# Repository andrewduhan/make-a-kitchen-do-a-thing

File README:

== Make A Kitchen Do A Thing ==

Preview: http://dl.dropbox.com/u/126001/circuits/kitchen-layout_and_board.jpg

=== Description ===
This is an Arduino clone with handy connections for 8 physical inputs and 8 high(er) current outputs, a built-in ULN2803 darlington array (http://www.ti.com/lit/ds/symlink/uln2803a.pdf), and selectable output voltage.  The project began as a way to add lights and stuff to my daughter's play kitchen, but turned into a more general-purpose board.

Inputs and outputs have 2.0mm JST right-angle locking connectors (http://media.digikey.com/pdf/Data%20Sheets/JST%20PDFs/PH%20Series.pdf).  There are also pads to wire in whatever you'd like.

=== Inputs ===
Four inputs are wired for switches (digital) and four have three pins to connect to a pot/knob (analog).  Of course you can use them all for something else entirely.   Each input has an LED that indicates the current state of that switch or knob.

=== Outputs ===
Devices connected to an output will see a voltage (either 5V or VIN) when the corresponding processor pin is set LOW. Each output can sink up to 500mA though the transistor, and I wouldn't sink more than 1500mA in total across all eight channels at any one time.  Six of the outputs are on PWM-capable channels.  Each output has an LED that indicates it's current state.

=== Power ===
9-24V DC into the barrel jack or directly onto the pads next to the barrel jack.  The Power LED will light when power is connected.
Output voltage can be set in the center-right of the board.
Set to 5V by wiring the VOUT pad to the 5V pad - this will cause all output power to come through the 7805 voltage regulator, and therefore limits your total current consumption to 1A.
Wiring the VOUT pad to the VIN pad will set your outputs to VIN, bypassing the regulator and allowing you to drive higher voltage devices like relays and motors.  The board's internal circuitry will still use 5V, only the output is changed.

=== Software ===
The arduino sketch "basic-kitchen.ino" causes the outputs to reflect the inputs.  This could be a good starting point for your projects.
The six FT232 pins in the center of the board will connect with a standard FTDI-style serial breakout board for programming via USB or such.

----

=== Build Notes ===
* Add the small parts first.
* If you don't like the LEDs, you don't need to install them.   They're just to make programming easier.
* I like to use a chip socket for the processor, but I suggest you solder the ULN2803 directly to the board so that it can thermally couple with the exposed copper beneath.  If you're going to sink a lot of current, maybe dab a bit of heatsink compound under there?

==== rev 19 ====
* The resistor network values aren't marked on the board, whoops.  4 of them are 1k, and the one right next to the processor is 10k.
* The voltage regulator section has markings for both 1000uf (solid line) and 100uf (dashed line) caps. If you're not going to pull a lot of current through the voltage regulator, you can use 100uf.  In BOTH cases, the NEGATIVE pin should go into the ROUND hole.  Whichever you choose, ignore the left over square pad.
* I goofed the silkscreen orientation markings for the LEDS, whoops.  The NEGATIVE/ANODE side with the SHORT pin should go into the ROUND pad.  The POSITIVE/CATHODE side with the LONG pin should go into the SQUARE hole.
* The holes for header pins (like the FT232 block) are really really tight with standard pins.  They'll fit, but you gotta work them gently/firmly back and forth.  Sorry about that.

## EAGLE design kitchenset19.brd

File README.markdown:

#Make A Kitchen Do A Thing

##Description

This is an Arduino clone with handy connections for eight physical inputs and eight high(er) current outputs, a built-in [ULN2803](http://www.ti.com/lit/ds/symlink/uln2803a.pdf) darlington array, per-pin LEDs for easy programming, and selectable output voltage.  The project began as a way to add lights and stuff to my daughter's play kitchen, but turned into a more general-purpose board.

Inputs and outputs have 2.0mm [JST right-angle locking connectors](http://media.digikey.com/pdf/Data%20Sheets/JST%20PDFs/PH%20Series.pdf).  There are also pads to wire in whatever you'd like.

The files were created in the free edition of CadSoft Eagle.

The board makes heavy use of curved traces simply because I think they look neat.  Unfortunately, curved traces are a pain in the ass to work with or edit;   I will add a straight-traces version soon.

###Inputs
Four inputs are wired with two pins for switches for [digital input](http://arduino.cc/en/Reference/digitalRead).  They are "ON" when the signal pin is pulled LOW (connected to the ground pin.) Four inputs have three pins for [analog input](http://arduino.cc/en/Reference/analogRead), like a knob.  This makes it easy to attach a pot to the ground and 5V pins, with the center (wiper) pin moving between 0 and 5V.  Of course you can use them all for something else entirely.  Each input has an LED that indicates the current state of that switch or knob.

###Outputs
Devices connected to an output will see a voltage ( either 5V or VIN, **minus the drop across the transistor**: 1V to 1.5V depending on current) when the corresponding processor pin is set HIGH.  Each output can sink up to 500mA though the transistor, and I wouldn't sink more than 1500mA in total across all eight channels at any one time.  Six of the outputs are on [PWM pins](http://arduino.cc/en/Reference/analogWrite), the other two can only output [On/Off](http://arduino.cc/en/Reference/digitalWrite).  Each output has an LED that indicates it's current state.

###Power
Supply 9-24V DC into the barrel jack or directly onto the pads next to the barrel jack.  The Power LED will light when power is connected.
Output voltage can be selected with the three larger pads marked VIN, VOUT, and 5V in the center-right of the board.
Wiring the VOUT pad to the 5V pad will cause all output power to come through the 7805 voltage regulator, and therefore limits your total current consumption to 1A.
Wiring the VOUT pad to the VIN pad will set your outputs to VIN, bypassing the regulator and allowing you to drive higher voltage devices like relays and motors.  The board's internal circuitry will still use 5V, only the output is changed.

###Software
The arduino sketch "basic-kitchen.ino" has constants defined for the I/O pins and simply makes the outputs to reflect the inputs.  This could be a good starting point for your projects.
The six FT232 pins in the center of the board will connect with a standard FTDI-style serial breakout board for programming via USB, [like this one](http://www.sparkfun.com/products/9716).

###Extras
The Arduino firmware gives the ATMega328 a total of twenty I/O pins.  On this board, sixteen of those are used for the main I/O and two are used for the serial FT232 block.  The remaining two unused pins (digital 2 and 4) are broken out to pads on the left side of the board.

----

###Build Notes
* Add the small parts first.
* If you don't like the LEDs, you don't need to install them.   They're just to make programming easier.
* I like to use a chip socket for the processor, but I suggest you solder the ULN2803 directly to the board so that it can thermally couple with the exposed copper beneath.  If you're going to sink a lot of current, maybe dab a bit of heatsink compound under there?
* Large capacitors:  the NEGATIVE pin goes in the ROUND hole.  The positive can go in either square hole, depending on the size of the cap.

###rev 19 issues
* Output connectors are wired with positive to the LEFT when you look at the board with outputs at the top.  This is actually backwards from what JST connectors usually do, so on pre-made connectors you will have BLACK = POSITIVE.  Whoops.
* The resistor network values aren't marked on the board, whoops.  They are all 1k.
* The voltage regulator section has markings for both 1000uf (solid line) and 100uf (dashed line) caps. If you're not going to pull a lot of current through the voltage regulator, you can use 100uf.  In BOTH cases, the NEGATIVE pin should go into the ROUND hole.  Whichever you choose, ignore the left over square pad.
* I goofed the silkscreen orientation markings for the LEDS, whoops.  The NEGATIVE/ANODE side with the SHORT pin should go into the ROUND pad.  The POSITIVE/CATHODE side with the LONG pin should go into the SQUARE hole.
Specifically: look at the board so you can read "Make a kitchen do a thing" and the outputs are at the top, inputs at the bottom.   All of the output LEDs should have their FLAT side to your LEFT.  The four input LEDs on the left (marked 12-15) should have their FLAT side to your RIGHT.  The other four input LEDS (marked A2-A5) should have their FLAT side to your LEFT.    
* The holes for header pins (like the FT232 block) are really really tight with standard pins.  They'll fit, but you gotta work them gently/firmly back and forth.  Sorry about that.

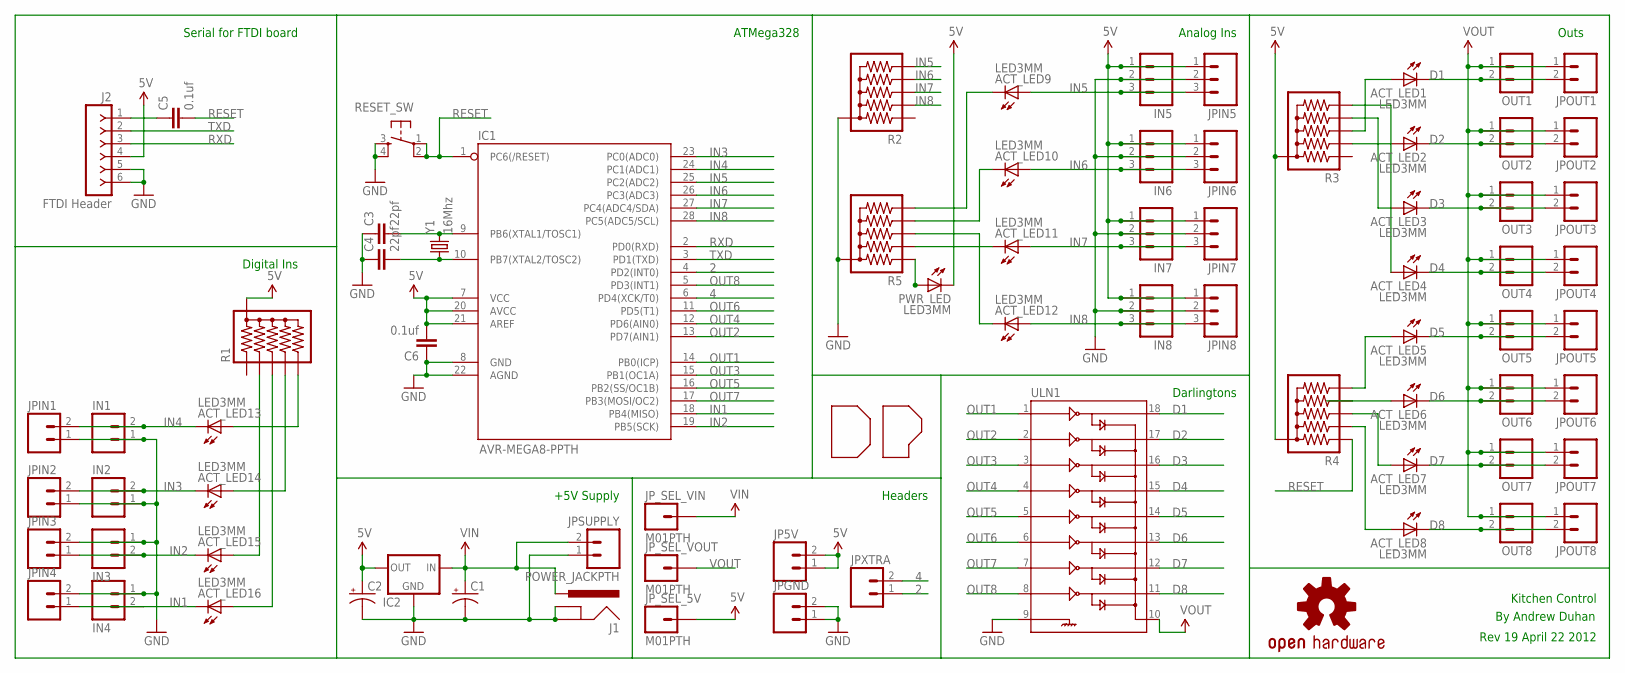
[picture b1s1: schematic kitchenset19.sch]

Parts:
ACT_LED1, ACT_LED2, ACT_LED3, ACT_LED4, ACT_LED5, ACT_LED6, ACT_LED7, ACT_LED8, ACT_LED9, ACT_LED10, ACT_LED11, ACT_LED12, ACT_LED13, ACT_LED14, ACT_LED15, ACT_LED16: LED3MM; LED3MM-POL
C1, C2: CAP_POLPTH4; CPOL-RADIAL-1000UF-25V
C3, C4: 22pf; CAP-PTH-SMALL
C5, C6: 0.1uf; CAP-PTH-SMALL
IC1: AVR-MEGA8-PPTH; DIL28-3
IC2: V_REG_78XXSIDE; 78XXL
IN1, IN2, IN3, IN4: M02JST-PTH-2; JST-2-PTH
IN5, IN6, IN7, IN8: M03JST-PTH; JST-3-PTH
J1: POWER_JACKPTH; POWER_JACK_PTH
J2: FTDI Header; SIP-100-06-32Y
JP5V: M02PTH; 1X02
JPGND: M02PTH; 1X02
JPIN1, JPIN2, JPIN3, JPIN4: M02PTH; 1X02
JPIN5, JPIN6, JPIN7, JPIN8: M03PTH; 1X03
JPOUT1, JPOUT2, JPOUT3, JPOUT4, JPOUT5, JPOUT6, JPOUT7, JPOUT8: M02PTH; 1X02
JPSUPPLY: M02PTH4; 1X02_XTRA_BIG
JPXTRA: M02PTH; 1X02
JP_SEL_5V: M01PTH; 1X01
JP_SEL_VIN: M01PTH; 1X01
JP_SEL_VOUT: M01PTH; 1X01
OUT1, OUT2, OUT3, OUT4, OUT5, OUT6, OUT7, OUT8: M02JST-PTH-2; JST-2-PTH
PWR_LED: LED3MM; LED3MM-POL
R1, R2, R3, R4, R5: RPACK-BUSSED-SIP-PTH-5; RPACK-SIP-PTH-5
RESET_SW: TAC_SWITCHPTH; TACTILE-PTH
U$1: OSHW-LOGOM; OSHW-LOGO-M
U$9: DP_LOGO
ULN1: ULN2803DIP; DIL18
Y1: 16Mhz; HC49US

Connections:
2: IC1.4 (PD2(INT0)), JPXTRA.1
4: IC1.6 (PD4(XCK/T0)), JPXTRA.2
5V: C2.1 (+), C6.2, IC1.7 (VCC), IC1.20 (AVCC), IC1.21 (AREF), IC2.OUT, IN5.1, IN6.1, IN7.1, IN8.1, J2.4, JP5V.1, JP5V.2, JPIN5.1, JPIN6.1, JPIN7.1, JPIN8.1, JP_SEL_5V.1, PWR_LED.K (C), R1.P$1 (1), R3.P$1 (1), R4.P$1 (1)
D1: ACT_LED1.K (C), JPOUT1.2, OUT1.2, ULN1.18
D2: ACT_LED2.K (C), JPOUT2.2, OUT2.2, ULN1.17
D3: ACT_LED3.K (C), JPOUT3.2, OUT3.2, ULN1.16
D4: ACT_LED4.K (C), JPOUT4.2, OUT4.2, ULN1.15
D5: ACT_LED5.K (C), JPOUT5.2, OUT5.2, ULN1.14
D6: ACT_LED6.K (C), JPOUT6.2, OUT6.2, ULN1.13
D7: ACT_LED7.K (C), JPOUT7.2, OUT7.2, ULN1.12
D8: ACT_LED8.K (C), JPOUT8.2, OUT8.2, ULN1.11
DTR: C5.1, J2.1
GND: C1.2 (-), C2.2 (-), C3.1, C4.1, C6.1, IC1.8 (GND), IC1.22 (AGND), IC2.GND, IN1.1, IN2.1, IN3.1, IN4.1, IN5.2, IN6.2, IN7.2, IN8.2, J1.GND, J1.GNDBREAK, J2.5, J2.6, JPGND.1, JPGND.2, JPIN1.1, JPIN2.1, JPIN3.2, JPIN4.2, JPIN5.2, JPIN6.2, JPIN7.2, JPIN8.2, JPSUPPLY.1, R2.P$1 (1), R5.P$1 (1), RESET_SW.3, RESET_SW.4, ULN1.9
IN1: ACT_LED16.K (C), IC1.18 (PB4(MISO)), IN4.2, JPIN4.1
IN2: ACT_LED15.K (C), IC1.19 (PB5(SCK)), IN3.2, JPIN3.1
IN3: ACT_LED14.K (C), IC1.23 (PC0(ADC0)), IN2.2, JPIN2.2
IN4: ACT_LED13.K (C), IC1.24 (PC1(ADC1)), IN1.2, JPIN1.2
IN5: ACT_LED9.A, IC1.25 (PC2(ADC2)), IN5.3, JPIN5.3, R2.P$6 (6)
IN6: ACT_LED10.A, IC1.26 (PC3(ADC3)), IN6.3, JPIN6.3, R2.P$5 (5)
IN7: ACT_LED11.A, IC1.27 (PC4(ADC4/SDA)), IN7.3, JPIN7.3, R2.P$4 (4)
IN8: ACT_LED12.A, IC1.28 (PC5(ADC5/SCL)), IN8.3, JPIN8.3, R2.P$3 (3)
unnamed: ACT_LED9.K (C), R5.P$6 (6)
unnamed: ACT_LED4.A, R3.P$6 (6)
unnamed: ACT_LED13.A, R1.P$6 (6)
unnamed: C4.2, IC1.10 (PB7(XTAL2/TOSC2)), Y1.1
unnamed: C3.2, IC1.9 (PB6(XTAL1/TOSC1)), Y1.2
unnamed: ACT_LED3.A, R3.P$5 (5)
unnamed: ACT_LED2.A, R3.P$3 (3)
unnamed: ACT_LED1.A, R3.P$4 (4)
unnamed: ACT_LED6.A, R4.P$5 (5)
unnamed: ACT_LED8.A, R4.P$3 (3)
unnamed: ACT_LED7.A, R4.P$4 (4)
unnamed: ACT_LED5.A, R4.P$6 (6)
unnamed: ACT_LED14.A, R1.P$5 (5)
unnamed: ACT_LED16.A, R1.P$4 (4)
unnamed: ACT_LED10.K (C), R5.P$5 (5)
unnamed: ACT_LED12.K (C), R5.P$4 (4)
unnamed: ACT_LED11.K (C), R5.P$3 (3)
unnamed: PWR_LED.A, R5.P$2 (2)
unnamed: ACT_LED15.A, R1.P$3 (3)
OUT1: IC1.14 (PB0(ICP)), ULN1.1
OUT2: IC1.13 (PD7(AIN1)), ULN1.2
OUT3: IC1.15 (PB1(OC1A)), ULN1.3
OUT4: IC1.12 (PD6(AIN0)), ULN1.4
OUT5: IC1.16 (PB2(SS/OC1B)), ULN1.5
OUT6: IC1.11 (PD5(T1)), ULN1.6
OUT7: IC1.17 (PB3(MOSI/OC2)), ULN1.7
OUT8: IC1.5 (PD3(INT1)), ULN1.8
RESET: C5.2, IC1.1 (PC6(/RESET)), R4.P$2 (2), RESET_SW.1, RESET_SW.2
RXD: IC1.2 (PD0(RXD)), J2.3
TXD: IC1.3 (PD1(TXD)), J2.2
VIN: C1.1 (+), IC2.IN, J1.PWR, JPSUPPLY.2, JP_SEL_VIN.1
VOUT: JPOUT1.1, JPOUT2.1, JPOUT3.1, JPOUT4.1, JPOUT5.1, JPOUT6.1, JPOUT7.1, JPOUT8.1, JP_SEL_VOUT.1, OUT1.1, OUT2.1, OUT3.1, OUT4.1, OUT5.1, OUT6.1, OUT7.1, OUT8.1, ULN1.10

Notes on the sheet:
Analog Ins
Darlingtons
Digital Ins
Serial for FTDI board
ATMega328
+5V Supply
Outs
Kitchen Control
Rev 19 April 22 2012
By Andrew Duhan
Headers

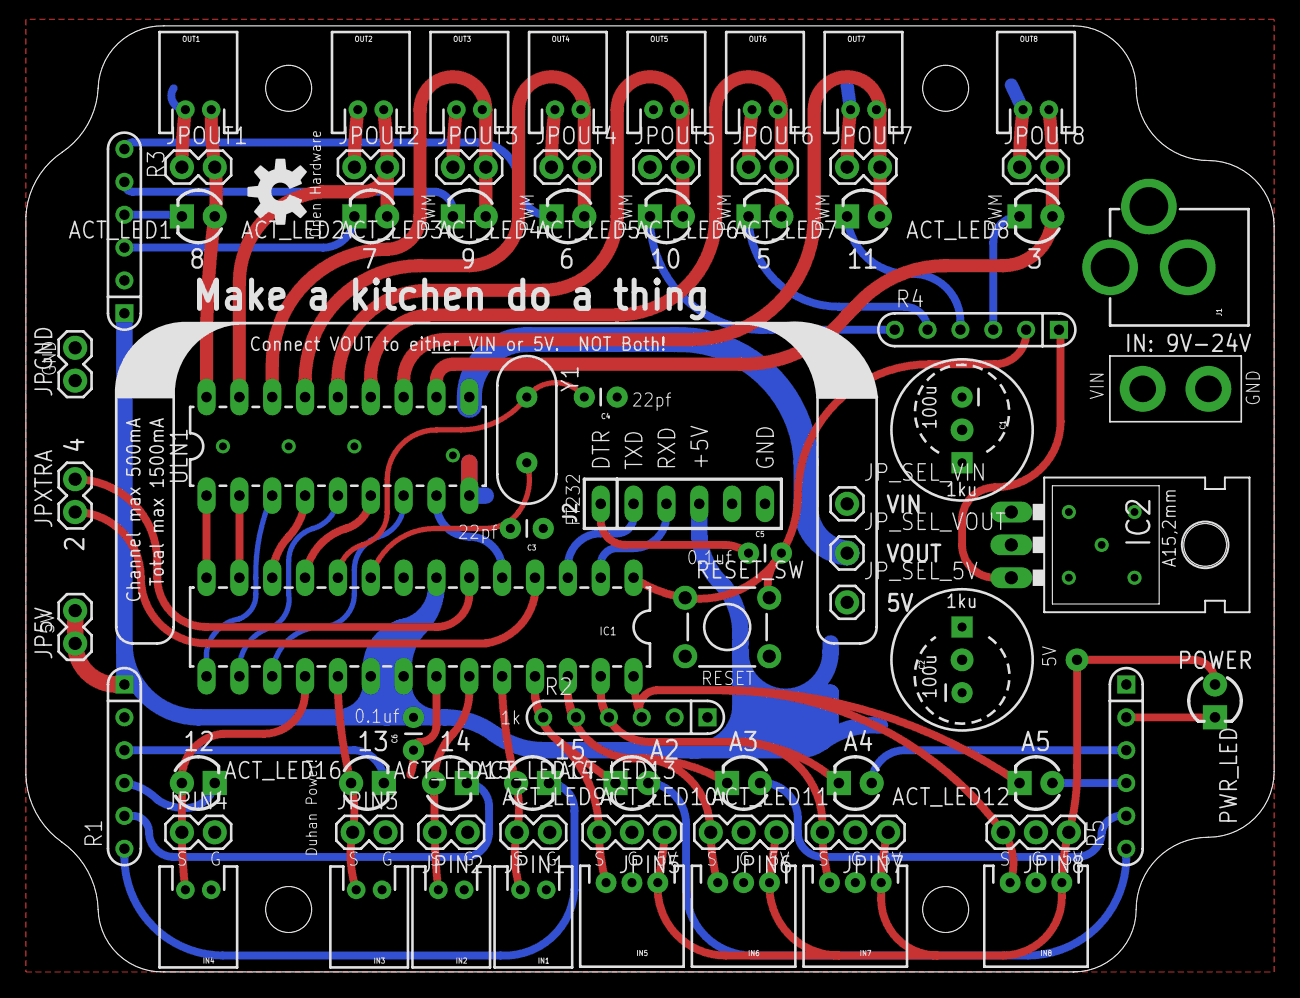
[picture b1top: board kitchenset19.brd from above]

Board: 2 copper layers, 96.5 x 73.2 mm, 76 parts (0 on the bottom side), 53 nets.

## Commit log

2012-05-15 initial commit, version 19.
2012-05-15 Readme + basic sketch
2012-05-15 readme changes
2012-05-15 change readme to markdown
2012-05-15 readme updates
2012-05-15 remove mediawiki readme
2012-05-16 fix example sketch, readme updates
2012-06-09 Update master
2013-06-05 fix incorrect pin assinments on DC barrel jack
2013-06-05 fix README
2013-06-05 smaller schematic.png
2013-06-05 less blurry schematic.png

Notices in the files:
parts and their libraries:
SparkFun: Licensing: CC v3.0 Share-Alike You are welcome to use this library for commercial purposes.
con-headers-jp: Copyright (C) 2008, Bob Starr
